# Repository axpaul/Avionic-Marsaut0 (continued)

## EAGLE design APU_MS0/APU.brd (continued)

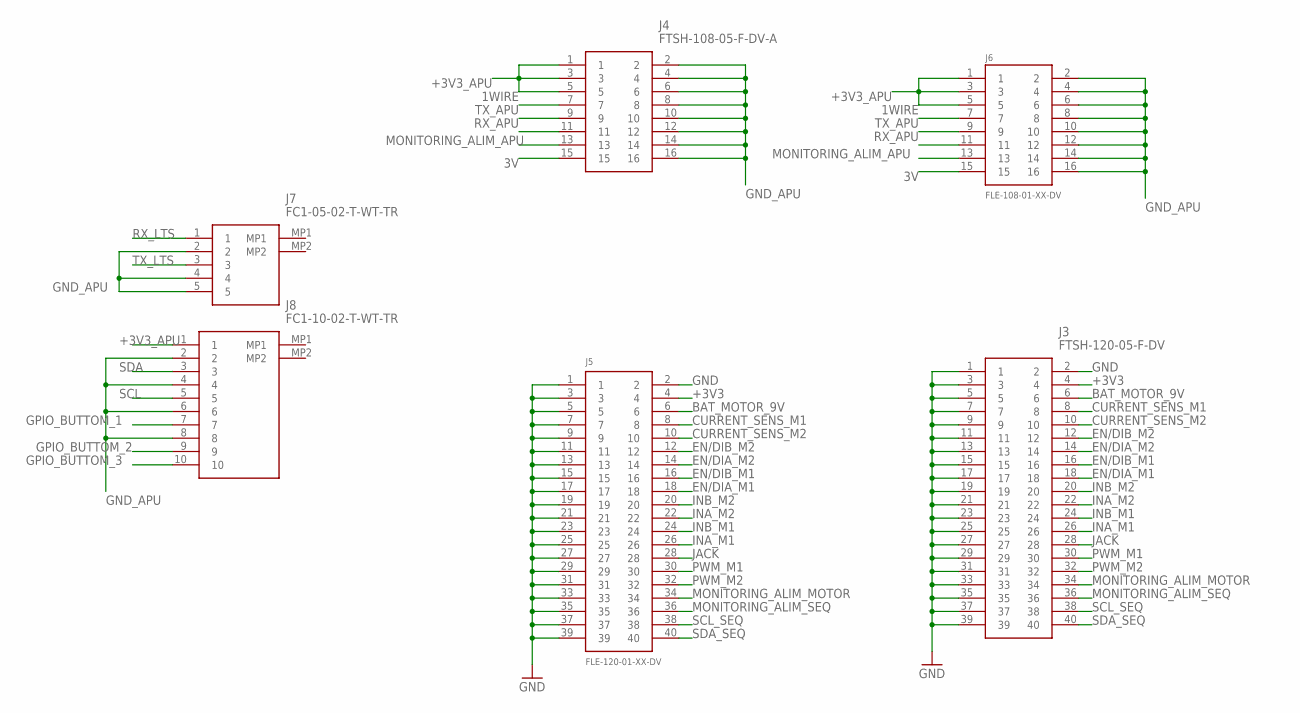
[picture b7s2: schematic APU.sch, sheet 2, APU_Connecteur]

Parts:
J3: FTSH-120-05-F-DV; FTSH-120-XX-YYY-DV
J4: FTSH-108-05-F-DV-A; FTSH-108-XX-YYY-DV-A
J5: FLE-120-01-XX-DV
J6: FLE-108-01-XX-DV
J7: FC1-05-02-T-WT-TR; FC10502TWTTR
J8: FC1-10-02-T-WT-TR; FC11002TWTTR

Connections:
1WIRE: J4.7, J6.7; also elsewhere on the board
3V: J4.15, J6.15; also elsewhere on the board
+3V3: J3.4, J5.4
+3V3_APU: J4.1, J4.3, J4.5, J6.1, J6.3, J6.5, J8.1; also elsewhere on the board
BAT_MOTOR_9V: J3.6, J5.6
CURRENT_SENS_M1: J3.8, J5.8
CURRENT_SENS_M2: J3.10, J5.10
EN/DIA_M1: J3.18, J5.18
EN/DIA_M2: J3.14, J5.14
EN/DIB_M1: J3.16, J5.16
EN/DIB_M2: J3.12, J5.12
GND: J3.1, J3.2, J3.3, J3.5, J3.7, J3.9, J3.11, J3.13, J3.15, J3.17, J3.19, J3.21, J3.23, J3.25, J3.27, J3.29, J3.31, J3.33, J3.35, J3.37, J3.39, J5.1, J5.2, J5.3, J5.5, J5.7, J5.9, J5.11, J5.13, J5.15, J5.17, J5.19, J5.21, J5.23, J5.25, J5.27, J5.29, J5.31, J5.33, J5.35, J5.37, J5.39
GND_APU: J4.2, J4.4, J4.6, J4.8, J4.10, J4.12, J4.14, J4.16, J6.2, J6.4, J6.6, J6.8, J6.10, J6.12, J6.14, J6.16, J7.2, J7.4, J7.5, J8.2, J8.4, J8.6, J8.8; also elsewhere on the board
GPIO_BUTTOM_1: J8.7; also elsewhere on the board
GPIO_BUTTOM_2: J8.9; also elsewhere on the board
GPIO_BUTTOM_3: J8.10; also elsewhere on the board
INA_M1: J3.26, J5.26
INA_M2: J3.22, J5.22
INB_M1: J3.24, J5.24
INB_M2: J3.20, J5.20
JACK: J3.28, J5.28
MONITORING_ALIM_APU: J4.13, J6.13; also elsewhere on the board
MONITORING_ALIM_MOTOR: J3.34, J5.34
MONITORING_ALIM_SEQ: J3.36, J5.36
PWM_M1: J3.30, J5.30
PWM_M2: J3.32, J5.32
RX_APU: J4.11, J6.11; also elsewhere on the board
RX_LTS: J7.1; also elsewhere on the board
SCL: J8.5; also elsewhere on the board
SCL_SEQ: J3.38, J5.38
SDA: J8.3; also elsewhere on the board
SDA_SEQ: J3.40, J5.40
TX_APU: J4.9, J6.9; also elsewhere on the board
TX_LTS: J7.3; also elsewhere on the board

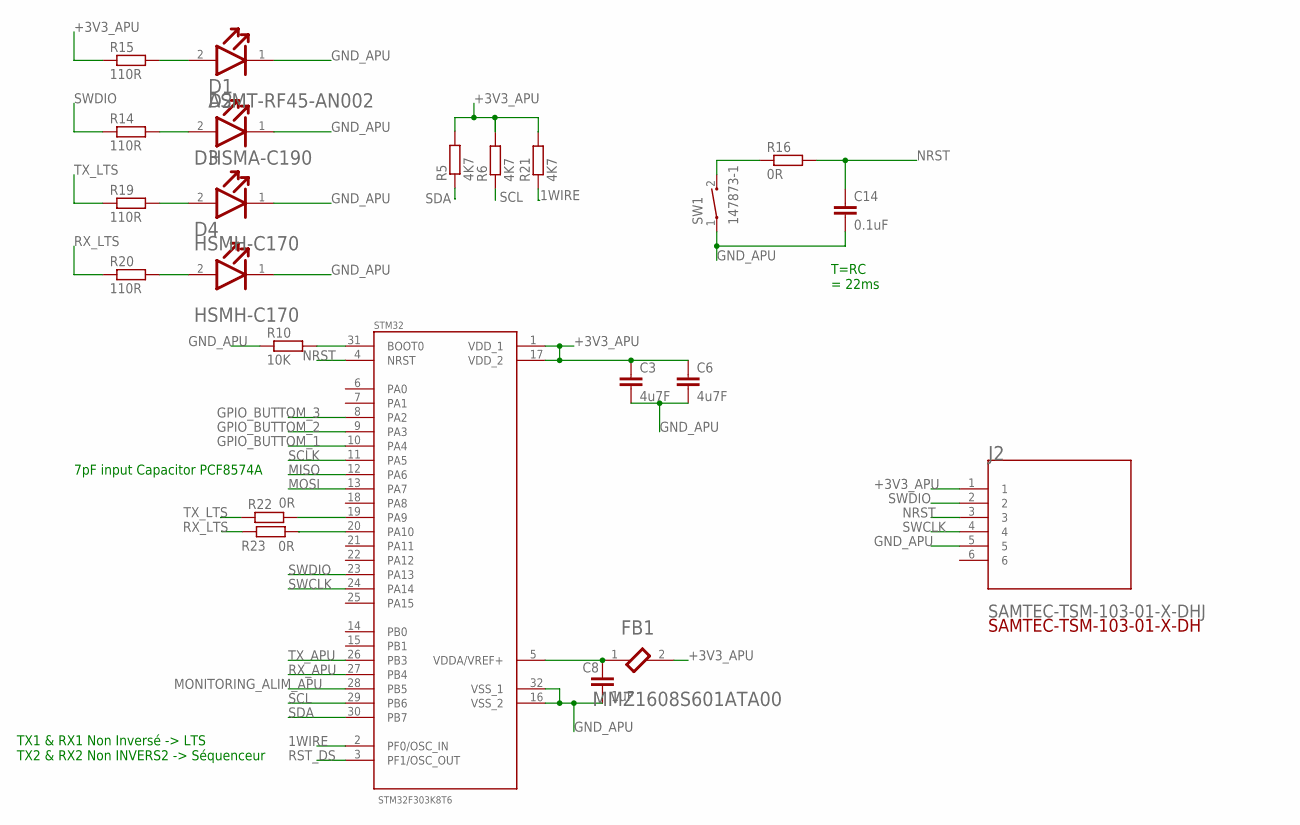
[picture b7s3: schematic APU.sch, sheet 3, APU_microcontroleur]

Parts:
C3, C6: 4u7F; C0805K
C8: 1uF; C0805K
C14: 0.1uF; C0805K
D1: BROADCOM_ASMT-RF45-AN002BROADCOM_ASMT-RF45-AN002_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; BROADCOM_ASMT-RF45-AN002_0
D2: BROADCOM_HSMA-C190BROADCOM_HSMA-C190_0_0; BROADCOM_HSMA-C190_0
D3, D4: BROADCOM_HSMH-C170BROADCOM_HSMH-C170_0_0; BROADCOM_HSMH-C170_0
FB1: TDK_MMZ1608S601ATA00TDK_MMZ1608S601ATA00_0_0; TDK_MMZ1608S601ATA00_0
J2: SAMTEC-TSM-103-01-X-DHJ; SAMTEC-TSM-103-01-X-DH
R5, R6, R21: 4K7; R0603
R10: 10K; R0603
R14, R15, R19, R20: 110R; R0603
R16, R22, R23: 0R; R0603
STM32: STM32F303K8T6; QFP80P900X900X160-32N
SW1: 147873-1; SW_147873-1

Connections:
1WIRE: R21.1, STM32.2 (PF0/OSC_IN); also elsewhere on the board
+3V3_APU: C3.1, C6.1, FB1.2, J2.1, R5.2, R6.2, R15.1, R21.2, STM32.1 (VDD_1), STM32.17 (VDD_2); also elsewhere on the board
GND_APU: C3.2, C6.2, C8.2, C14.2, D1.1 (CATHODE), D2.1 (CATHODE), D3.1 (CATHODE), D4.1 (CATHODE), J2.5, R10.1, STM32.16 (VSS_2), STM32.32 (VSS_1), SW1.1; also elsewhere on the board
GPIO_BUTTOM_1: STM32.10 (PA4); also elsewhere on the board
GPIO_BUTTOM_2: STM32.9 (PA3); also elsewhere on the board
GPIO_BUTTOM_3: STM32.8 (PA2); also elsewhere on the board
MISO: STM32.12 (PA6); also elsewhere on the board
MONITORING_ALIM_APU: STM32.28 (PB5); also elsewhere on the board
MOSI: STM32.13 (PA7); also elsewhere on the board
unnamed: C8.1, FB1.1, STM32.5 (VDDA/VREF+)
unnamed: R10.2, STM32.31 (BOOT0)
unnamed: D1.2 (ANODE), R15.2
unnamed: D3.2 (ANODE), R19.2
unnamed: D4.2 (ANODE), R20.2
unnamed: R22.2, STM32.19 (PA9)
unnamed: R23.2, STM32.20 (PA10)
unnamed: D2.2 (ANODE), R14.2
unnamed: R16.1, SW1.2
NRST: C14.1, J2.3, R16.2, STM32.4 (NRST)
RST_DS: STM32.3 (PF1/OSC_OUT); also elsewhere on the board
RX_APU: STM32.27 (PB4); also elsewhere on the board
RX_LTS: R20.1, R23.1; also elsewhere on the board
SCL: R6.1, STM32.29 (PB6); also elsewhere on the board
SCLK: STM32.11 (PA5); also elsewhere on the board
SDA: R5.1, STM32.30 (PB7); also elsewhere on the board
SWCLK: J2.4, STM32.24 (PA14)
SWDIO: J2.2, R14.1, STM32.23 (PA13)
TX_APU: STM32.26 (PB3); also elsewhere on the board
TX_LTS: R19.1, R22.1; also elsewhere on the board

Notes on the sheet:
7pF input Capacitor PCF8574A
TX1 & RX1 Non Inversé -> LTS TX2 & RX2 Non INVERS2 -> Séquenceur
T=RC = 22ms

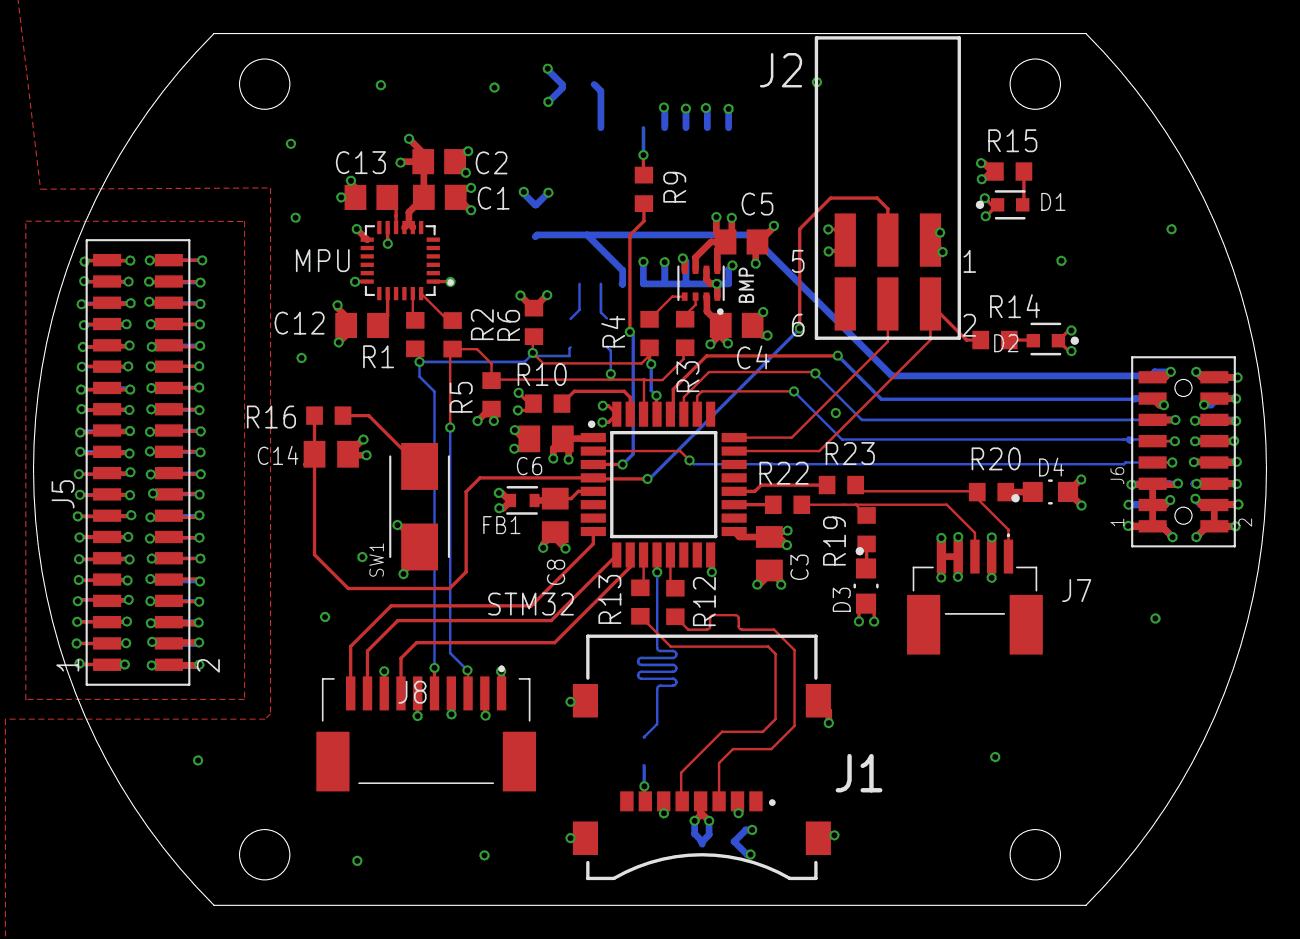
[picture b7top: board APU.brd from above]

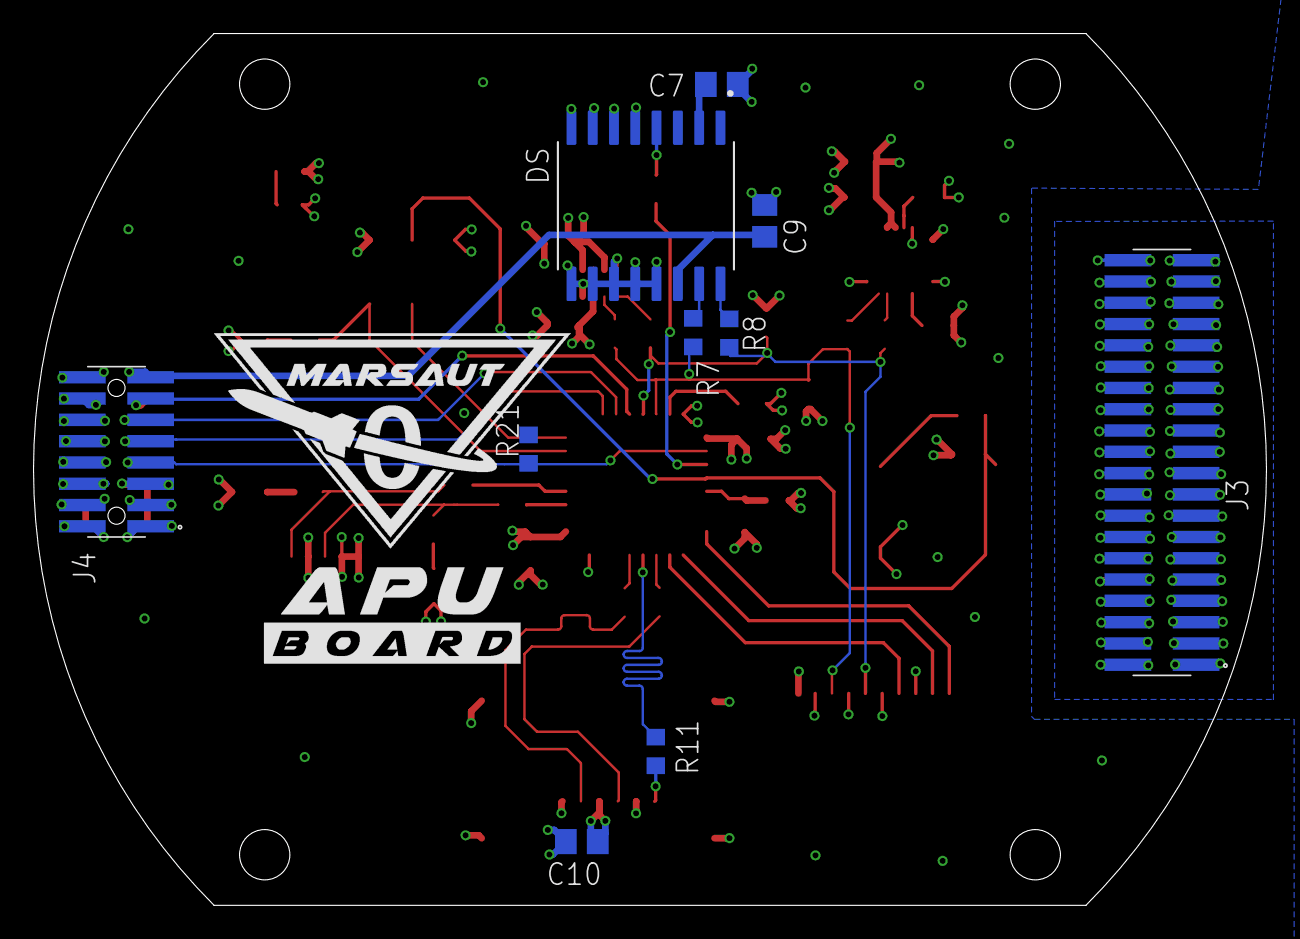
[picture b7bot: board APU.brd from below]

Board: 4 copper layers, 73.5 x 52.0 mm, 52 parts (10 on the bottom side), 62 nets.

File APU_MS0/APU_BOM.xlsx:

Qty | Value | MPN | Package | Parts
13 | 0R | CRCW06030000Z0EAC | R0603 | R1, R2, R3, R4, R7, R8, R9, R11, R12, R13, R16, R22, R23
8 | 100nF | C0805X104M5RACTU | C0805 | C1, C2, C4, C5, C7, C9, C10, C13
1 | 10K | ERJ-UP3F1002V | R0603 | R10
4 | 110R | ERJ-UP3F1100V | R0603 | R14, R15, R19, R20
1 | 147873-1 |  | SMT | SW1
1 | 1uF | C0805X105K3RAC3316 | C0805K | C8
1 | 2.2nF | C0805C222K3GECTU | C0805 | C12
1 | 0.1uF | C0805C225K3RACTU | C0805 | C14
3 | 4K7 | ERJ-UP3D4701V | R0603 | R5, R6, R21
2 | 4u7F | C0805C475K3RACTU | C0805 | C3, C6
1 | BMP280 | AliExpress | SMT | BMP
1 | BROADCOM_ASMT-RF45-AN002BROADCOM_ASMT-RF45-AN002_0_0 | ASMT-RF45-AN002 | SMT | D1
1 | BROADCOM_HSMA-C190BROADCOM_HSMA-C190_0_0 | HSMA-C190 | SMT | D2
2 | BROADCOM_HSMH-C170BROADCOM_HSMH-C170_0_0 | HSMH-C170 | SMT | D3, D4
1 | DS3231S | DS3231S# | SOIC127P1032X265-16N | DS
1 | FC1-05-02-T-WT-TR | FC1-05-02-T-WT-TR | SMT | J7
1 | FC1-10-02-T-WT-TR | FC1-10-02-T-WT | SMT | J8
1 | FLE-108-01-XX-DV | FLE-108-01-G-DV | SMT | J6
1 | FLE-120-01-XX-DV | FLE-120-01-G-DV | SMT | J5
1 | FTSH-108-05-F-DV-A | FTSH-108-05-F-DV-A | SMT | J4
1 | FTSH-120-05-F-DV | FTSH-120-05-F-DV | SMT | J3
1 | MEM2067-02-180-00-A_REVB |  | SMT | J1
1 | MPU-6050 | MPU-6050 | QFN50P400X400X95-24N | MPU
1 | SAMTEC-TSM-103-01-X-DHJ | TSM-103-01-F-DV-P-TR | SMT | J2
1 | SN74LVC1G17DCKR | SN74LVC1G17DCKR | SOT65P210X110-5N | SN74
1 | STM32F303K8T6 | STM32F303K8T6 | QFP80P900X900X160-32N | STM32
1 | TDK_MMZ1608S601ATA00TDK_MMZ1608S601ATA00_0_0 | MMZ1608S601ATA00 | SMT | FB1

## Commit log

2021-10-09 Apu board add
2021-10-09 SEQ board add
2021-10-09 ALIM board add
2021-10-09 IHM board add
2021-10-09 LINK board add
2021-10-09 MOTOR board add
2021-10-09 INT_LTS board add
2021-10-09 add component lib eagle
2021-10-15 add pictures
2021-10-15 add all schematic
2021-12-20 last version2
2022-06-17 Update LICENSE
2022-06-17 Create Licence
2023-07-28 Update Licence
